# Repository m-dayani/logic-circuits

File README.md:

# logic-circuits
Experimental project working with logic gates. Learn how a group of transistors create logic gates and how we can build useful combinational and sequential circuites using logic gates.

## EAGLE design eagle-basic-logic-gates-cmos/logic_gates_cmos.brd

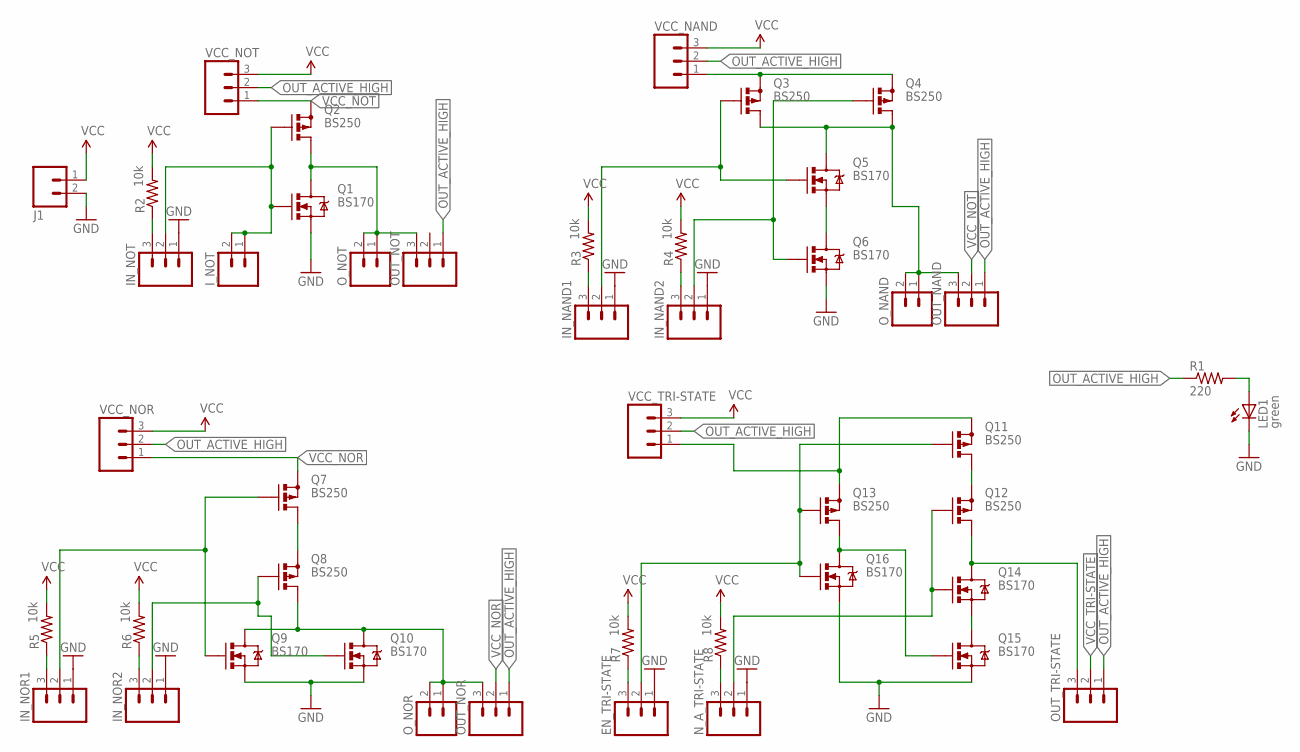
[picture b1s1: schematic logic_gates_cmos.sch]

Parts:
EN_TRI-STATE: M03LONGPADS; 1X03_LONGPADS
IN_NAND1, IN_NAND2: M03LONGPADS; 1X03_LONGPADS
IN_NOR1, IN_NOR2: M03LONGPADS; 1X03_LONGPADS
IN_NOT: M03LONGPADS; 1X03_LONGPADS
I_NOT: M02PTH; 1X02
J1: M02LOCK_LONGPADS; 1X02_LOCK_LONGPADS
LED1: green; LED3MM
N_A_TRI-STATE: M03LONGPADS; 1X03_LONGPADS
OUT_NAND: M03LONGPADS; 1X03_LONGPADS
OUT_NOR: M03LONGPADS; 1X03_LONGPADS
OUT_NOT: M03LONGPADS; 1X03_LONGPADS
OUT_TRI-STATE: M03LONGPADS; 1X03_LONGPADS
O_NAND: M02PTH; 1X02
O_NOR: M02PTH; 1X02
O_NOT: M02PTH; 1X02
Q1, Q5, Q6, Q9, Q10, Q14, Q15, Q16: BS170; TO92-OVAL
Q2, Q3, Q4, Q7, Q8, Q11, Q12, Q13: BS250; TO92-OVAL
R1: 220; AXIAL-0.4
R2, R3, R4, R5, R6, R7, R8: 10k; AXIAL-0.4
VCC_NAND: M03LONGPADS; 1X03_LONGPADS
VCC_NOR: M03LONGPADS; 1X03_LONGPADS
VCC_NOT: M03LONGPADS; 1X03_LONGPADS
VCC_TRI-STATE: M03LONGPADS; 1X03_LONGPADS

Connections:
GND: EN_TRI-STATE.1, IN_NAND1.1, IN_NAND2.1, IN_NOR1.1, IN_NOR2.1, IN_NOT.1, J1.2, LED1.K (C), N_A_TRI-STATE.1, Q1.3 (S), Q6.3 (S), Q9.3 (S), Q10.3 (S), Q15.3 (S), Q16.3 (S)
unnamed: OUT_NAND.3, O_NAND.1, O_NAND.2, Q3.1 (D), Q4.1 (D), Q5.1 (D)
unnamed: IN_NOR1.2, Q7.2 (G), Q9.2 (G)
unnamed: Q3.3 (S), Q4.3 (S), VCC_NAND.1
unnamed: IN_NOR1.3, R5.P$1 (1)
unnamed: Q5.3 (S), Q6.1 (D)
unnamed: IN_NOR2.2, Q8.2 (G), Q10.2 (G)
unnamed: IN_NOR2.3, R6.P$1 (1)
unnamed: OUT_NOT.3, O_NOT.1, O_NOT.2, Q1.1 (D), Q2.1 (D)
unnamed: OUT_NOR.3, O_NOR.1, O_NOR.2, Q8.1 (D), Q9.1 (D), Q10.1 (D)
unnamed: Q7.1 (D), Q8.3 (S)
unnamed: EN_TRI-STATE.2, Q11.2 (G), Q13.2 (G), Q16.2 (G)
unnamed: EN_TRI-STATE.3, R7.P$1 (1)
unnamed: LED1.A, R1.P$2 (2)
unnamed: IN_NOT.2, I_NOT.1, I_NOT.2, Q1.2 (G), Q2.2 (G)
unnamed: IN_NAND2.2, Q4.2 (G), Q6.2 (G)
unnamed: Q13.1 (D), Q15.2 (G), Q16.1 (D)
unnamed: Q11.1 (D), Q12.3 (S)
unnamed: Q14.3 (S), Q15.1 (D)
unnamed: IN_NOT.3, R2.P$1 (1)
unnamed: IN_NAND1.2, Q3.2 (G), Q5.2 (G)
unnamed: N_A_TRI-STATE.2, Q12.2 (G), Q14.2 (G)
unnamed: IN_NAND1.3, R3.P$1 (1)
unnamed: IN_NAND2.3, R4.P$1 (1)
unnamed: N_A_TRI-STATE.3, R8.P$1 (1)
unnamed: OUT_TRI-STATE.3, Q12.1 (D), Q14.1 (D)
OUT_ACTIVE_HIGH: OUT_NAND.1, OUT_NOR.1, OUT_NOT.1, OUT_TRI-STATE.1, R1.P$1 (1), VCC_NAND.2, VCC_NOR.2, VCC_NOT.2, VCC_TRI-STATE.2
VCC: J1.1, R2.P$2 (2), R3.P$2 (2), R4.P$2 (2), R5.P$2 (2), R6.P$2 (2), R7.P$2 (2), R8.P$2 (2), VCC_NAND.3, VCC_NOR.3, VCC_NOT.3, VCC_TRI-STATE.3
VCC_NOR: OUT_NOR.2, Q7.3 (S), VCC_NOR.1
VCC_NOT: OUT_NAND.2, Q2.3 (S), VCC_NOT.1
VCC_TRI-STATE: OUT_TRI-STATE.2, Q11.3 (S), Q13.3 (S), VCC_TRI-STATE.1

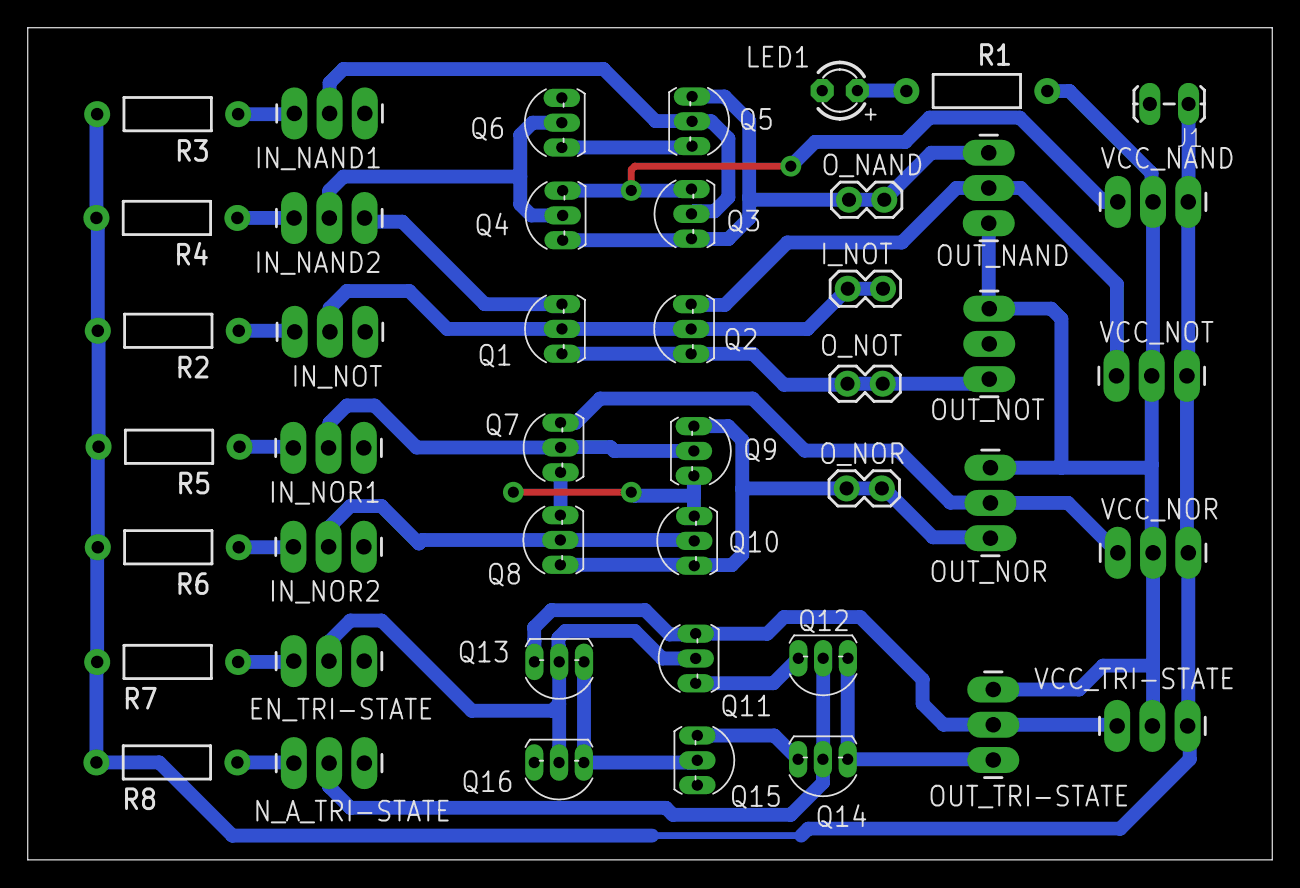
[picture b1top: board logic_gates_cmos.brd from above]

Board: 2 copper layers, 89.7 x 60.0 mm, 45 parts (0 on the bottom side), 31 nets.

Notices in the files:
parts and their libraries:
SparkFun-Connectors: Licensing: Creative Commons ShareAlike 4.0 International - https://creativecommons.org/licenses/by-sa/4.0
